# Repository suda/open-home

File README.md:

Open Home
=========

A collection of schematics, code and ideas for cheap, DIY connected home solution.

Whole documentation is available [on the Wiki](https://github.com/appsome/open-home/wiki).

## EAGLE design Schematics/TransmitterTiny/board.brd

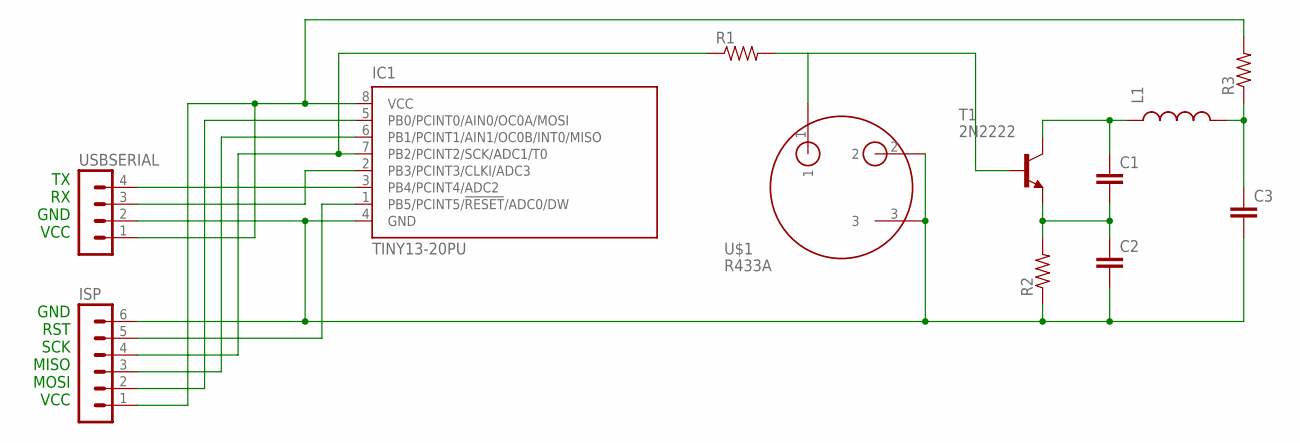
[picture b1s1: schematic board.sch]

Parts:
C1, C2: CAPPTH; CAP-PTH-SMALL
C3: CAPPTH1; CAP-PTH-5MM
IC1: TINY13-20PU; DIL08
ISP: MA06-1
L1: INDUCTORAXIAL-0.6; AXIAL-0.6
R1, R2, R3: RESISTORAXIAL-0.3; AXIAL-0.3
T1: 2N2222; TO92-EBC-OVAL
U$1: R433A; TO-39
USBSERIAL: MA04-1

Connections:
unnamed: IC1.8 (VCC), ISP.1, R3.P$2 (2), USBSERIAL.1
unnamed: IC1.2 (PB3/PCINT3/CLKI/ADC3), USBSERIAL.3
unnamed: IC1.3 (PB4/PCINT4/ADC2), USBSERIAL.4
unnamed: IC1.7 (PB2/PCINT2/SCK/ADC1/T0), ISP.4, R1.P$1 (1)
unnamed: R1.P$2 (2), T1.B, U$1.1
unnamed: C3.1, L1.P$2 (2), R3.P$1 (1)
unnamed: C2.2, C3.2, IC1.4 (GND), ISP.6, R2.P$1 (1), U$1.2, U$1.3, USBSERIAL.2
unnamed: C1.2, C2.1, R2.P$2 (2), T1.E
unnamed: C1.1, L1.P$1 (1), T1.C
unnamed: IC1.1 (PB5/PCINT5/!RESET!/ADC0/DW), ISP.5
unnamed: IC1.6 (PB1/PCINT1/AIN1/OC0B/INT0/MISO), ISP.3
unnamed: IC1.5 (PB0/PCINT0/AIN0/OC0A/MOSI), ISP.2

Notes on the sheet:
TX RX GND VCC
GND RST SCK MISO MOSI VCC

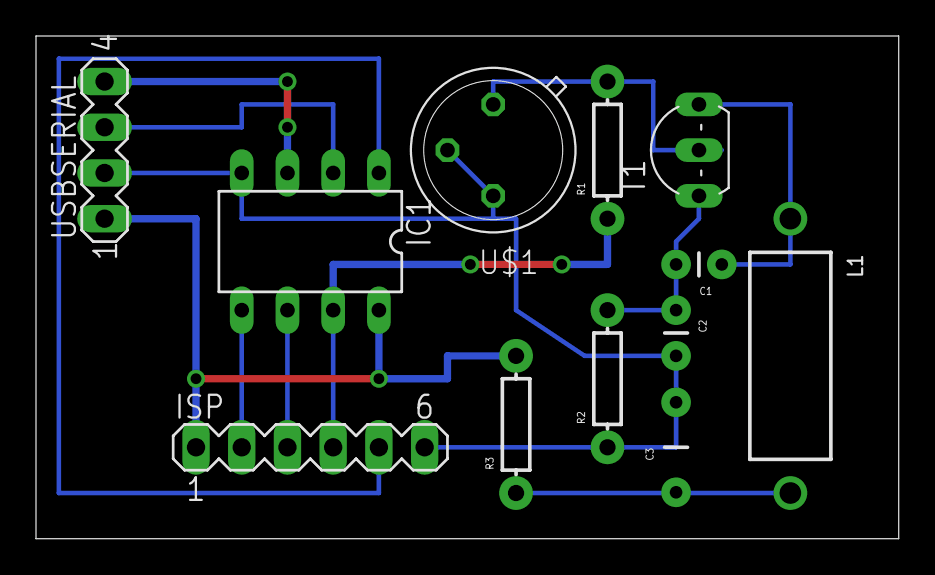
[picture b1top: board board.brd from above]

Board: 2 copper layers, 47.9 x 27.9 mm, 12 parts (0 on the bottom side), 12 nets.

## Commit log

2013-11-04 Added Arduino bridge code
2013-11-04 Added BasicWebserver Python code
2013-11-04 Added setting pulse length
2013-11-05 Added Clarus remote PCB photo
2013-11-05 Update README.md with Wiki link
2013-11-06 Updated comment.
2013-11-07 Added bridge code ported to ATTiny 45/85 microcontrollers
2013-11-07 Remove echo and leave more verbose response
2013-11-07 Added tweaked Arduino ISP working with ATTiny microcontrollers
2013-11-08 Reopening connection
2013-11-13 Moved pin declaration
2013-11-13 Added icons for BasicWebserver
2013-11-13 Added ability to send multiple messages
2013-11-17 Bridge ported to Arduino Yun
2013-11-17 Code cleanup
2013-11-18 Return JSON
2013-11-18 Added recorder remote codes
2013-11-18 Renamed Bridge to Transmitter (to avoid confusion with Yun's Bridge library)
2013-11-19 ATtiny85 transmitter board. Work in progress
2013-11-20 Refactored API to be compatible with Yun port
2013-11-20 Added Clarus set 1454
2013-11-20 Fixed Yun transmitter
2013-11-21 Finished board
2013-11-22 Stub for iOS app
2013-11-24 Working gestures
2013-11-24 Added Podfile
2013-11-25 Left and right panels
2013-11-25 Added icons and launch images
2013-11-25 Minor tweaks
2013-11-26 Save server address
2013-11-26 Added calling viewWillAppear: for left/right panel
2013-12-14 Changed transmitter pin to #9
2013-12-15 Added ATtiny85 perfboard schematics
2013-12-19 Ignore PyCharm files
2013-12-27 Webserver using Django and Celery
2014-01-04 Send command after adding
2014-01-04 Improved admin
2014-01-04 Working on iOS app
2014-01-19 Fully working API
2014-01-19 Renamed core to api
2014-01-20 Removed prints
2014-01-20 Simple web app for controlling groups
2014-01-20 Fixed cache
2014-01-20 Reset migrations
2014-01-20 Added management command for listing available ports
2014-01-21 Removed deprecated BasecWebserver
2014-01-21 Voice control (in Polish for now)
2014-01-22 Decreased pooling interval for celery
2014-01-25 Transmitter is now Transceiver
2014-03-27 Added set 1428
2014-03-27 Fixes in Yun transmitter
2014-03-27 Added index.html and redirect in send command
2014-03-27 Codes for set with detailed devices
2014-07-26 Added Kemot remotes
2020-05-26 Bump requests from 2.2.0 to 2.20.0 in /Python/listen
    Bumps [requests](https://github.com/psf/requests) from 2.2.0 to 2.20.0.
    - [Release notes](https://github.com/psf/requests/releases)
    - [Changelog](https://github.com/psf/requests/blob/master/HISTORY.md)
    - [Commits](https://github.com/psf/requests/compare/v2.2.0...v2.20.0)
2020-05-26 Bump djangorestframework from 2.3.12 to 3.9.1 in /Python/webserver
    Bumps [djangorestframework](https://github.com/encode/django-rest-framework) from 2.3.12 to 3.9.1.
    - [Release notes](https://github.com/encode/django-rest-framework/releases)
    - [Commits](https://github.com/encode/django-rest-framework/compare/2.3.12...3.9.1)
2020-05-26 Bump django from 1.6.1 to 1.11.28 in /Python/webserver
    Bumps [django](https://github.com/django/django) from 1.6.1 to 1.11.28.
    - [Release notes](https://github.com/django/django/releases)
    - [Commits](https://github.com/django/django/compare/1.6.1...1.11.28)

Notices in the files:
parts and their libraries:
SparkFun-Passives: Licensing: CC v3.0 Share-Alike You are welcome to use this library for commercial purposes.
